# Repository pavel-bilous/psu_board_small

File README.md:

# PSU board

Revision 2 screenshots:

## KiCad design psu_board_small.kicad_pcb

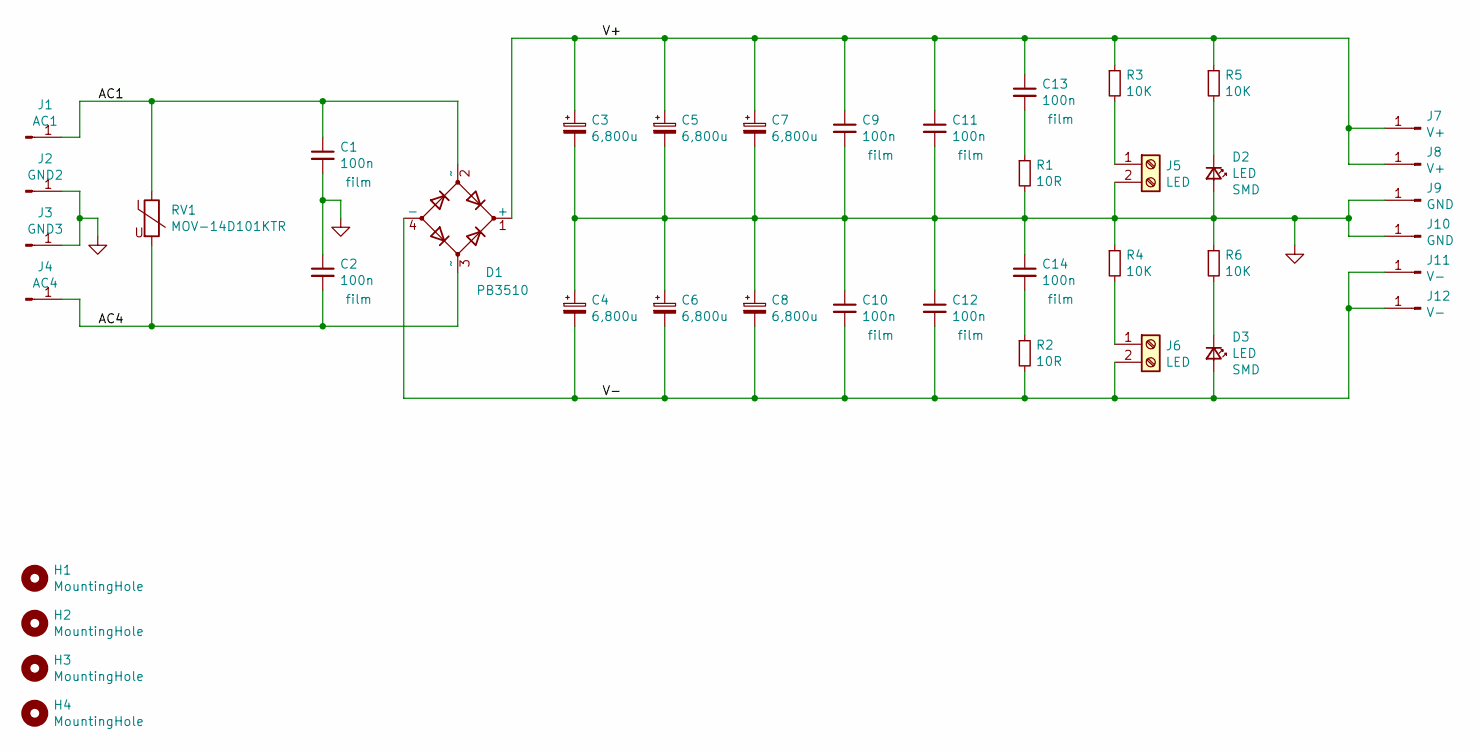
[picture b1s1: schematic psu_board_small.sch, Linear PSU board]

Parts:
C1, C2, C9, C10, C11, C12, C13, C14: 100n; C_Rect_L7.2mm_W2.5mm_P5.00mm_FKS2_FKP2_MKS2_MKP2
C3, C4, C5, C6, C7, C8: 6,800u; CP_Radial_D25.0mm_P10.00mm_SnapIn
D1: PB3510; PB3510E345
D2, D3: LED; D_0805_2012Metric_Pad1.15x1.40mm_HandSolder
H1, H2, H3, H4: MountingHole; MountingHole_3.2mm_M3_Pad_Via
J1: AC1; Terminal_.25_PCB_TAB_TE_Connectivity_P5.08mm_
J2: GND2; Terminal_.25_PCB_TAB_TE_Connectivity_P5.08mm_
J3: GND3; Terminal_.25_PCB_TAB_TE_Connectivity_P5.08mm_
J4: AC4; Terminal_.25_PCB_TAB_TE_Connectivity_P5.08mm_
J5, J6: LED; TerminalBlock_MetzConnect_Type059_RT06302HBWC_1x02_P3.50mm_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
J7, J8: V+; Terminal_.25_PCB_TAB_TE_Connectivity_P5.08mm_
J9, J10: GND; Terminal_.25_PCB_TAB_TE_Connectivity_P5.08mm_
J11, J12: V-; Terminal_.25_PCB_TAB_TE_Connectivity_P5.08mm_
R1, R2: 10R; R_Axial_DIN0207_L6.3mm_D2.5mm_P10.16mm_Horizontal
R3, R4, R5, R6: 10K; R_Axial_DIN0207_L6.3mm_D2.5mm_P10.16mm_Horizontal
RV1: MOV-14D101KTR; RV_Disc_D15.5mm_W3.9mm_P7.5mm

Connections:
/AC1: C1.1, D1.2 (~~), J1.1, RV1.1
/AC4: C2.2, D1.3 (~~), J4.1, RV1.2
/V+: C3.1, C5.1, C7.1, C9.1, C11.1, C13.1, D1.1 (+), J7.1, J8.1, R3.1, R5.1
/V-: C4.2, C6.2, C8.2, C10.2, C12.2, D1.4 (-), D3.2 (A), J6.2, J11.1, J12.1, R2.2
GND: C1.2, C2.1, C3.2, C4.1, C5.2, C6.1, C7.2, C8.1, C9.2, C10.1, C11.2, C12.1, C14.1, D2.2 (A), J2.1, J3.1, J5.2, J9.1, J10.1, R1.2, R4.1, R6.1
unnamed: C13.2, R1.1
unnamed: C14.2, R2.1
unnamed: D2.1 (K), R5.2
unnamed: D3.1 (K), R6.2
unnamed: J5.1, R3.2
unnamed: J6.1, R4.2

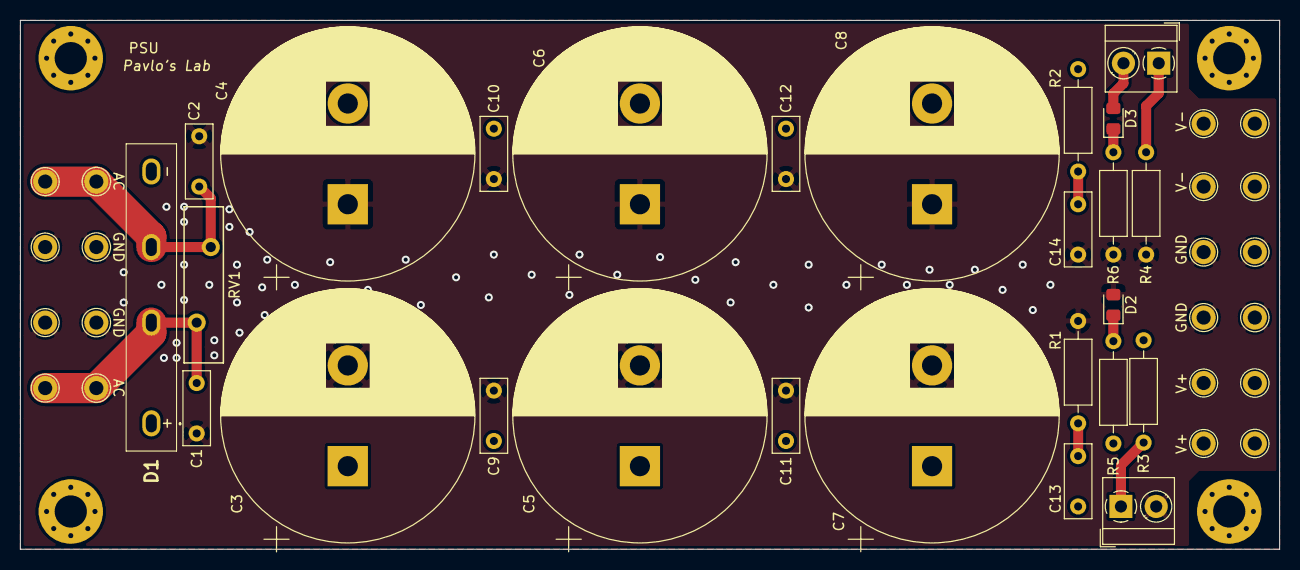
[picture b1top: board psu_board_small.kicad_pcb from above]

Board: 2 copper layers, 125.0 x 52.5 mm, 40 parts (0 on the bottom side), 11 nets.

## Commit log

2023-06-29 added sch
2023-07-08 finished pcb layout
2023-07-08 grb file
2023-12-23 adds licence and gitignore
2023-12-23 updated rev2
